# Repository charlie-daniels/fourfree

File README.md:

# fourfree - 43 key keeb

Designed because nobody sells 40-ish percent keyboards anymore.

## PCB

Created using KiCad with [marbastlib](https://github.com/ebastler/marbastlib) and a few handmade footprints.

Created Oct 2024.

## Assembly

**ProMicro goes in upsidedown on the topside!!!**
This is why the pads are on the bottom and the pin labels seem flipped from the top.

### Components 

**PCB** 

- 43x 1N4148W Diodes
- 43x Kailh Hotswap MX
- 1x Sparkfun Promicro
- 1x 2-pin Reset switch
- 1x 128x32 OLED (optional)
- 1x 2.75u PCB mount stabiliser
- 1x 2.25u PCB mount stabiliser
- 1x 2u PCB mount stabiliser

**Case**

- 14x M2 screws...?
Case still being designed but should be screw in to the pcb mounting brackets, maybe 14 was overkill...

## Firmware

This is just initial firmware made with [Keyboard Firmware Builder](https://kbfirmware.com/) by [Ruiqi Mao](https://ruiqimao.com/). The keymaps should work as expected as they are configured properly with the pinouts and key matrix.

## In Progress...

- Plate
- Case
- To see if the pcb actually works...

## Thanks

[Ben Vallack](https://www.youtube.com/channel/UC4NNPgQ9sOkBjw6GlkgCylg)'s YouTube tutorials are great.

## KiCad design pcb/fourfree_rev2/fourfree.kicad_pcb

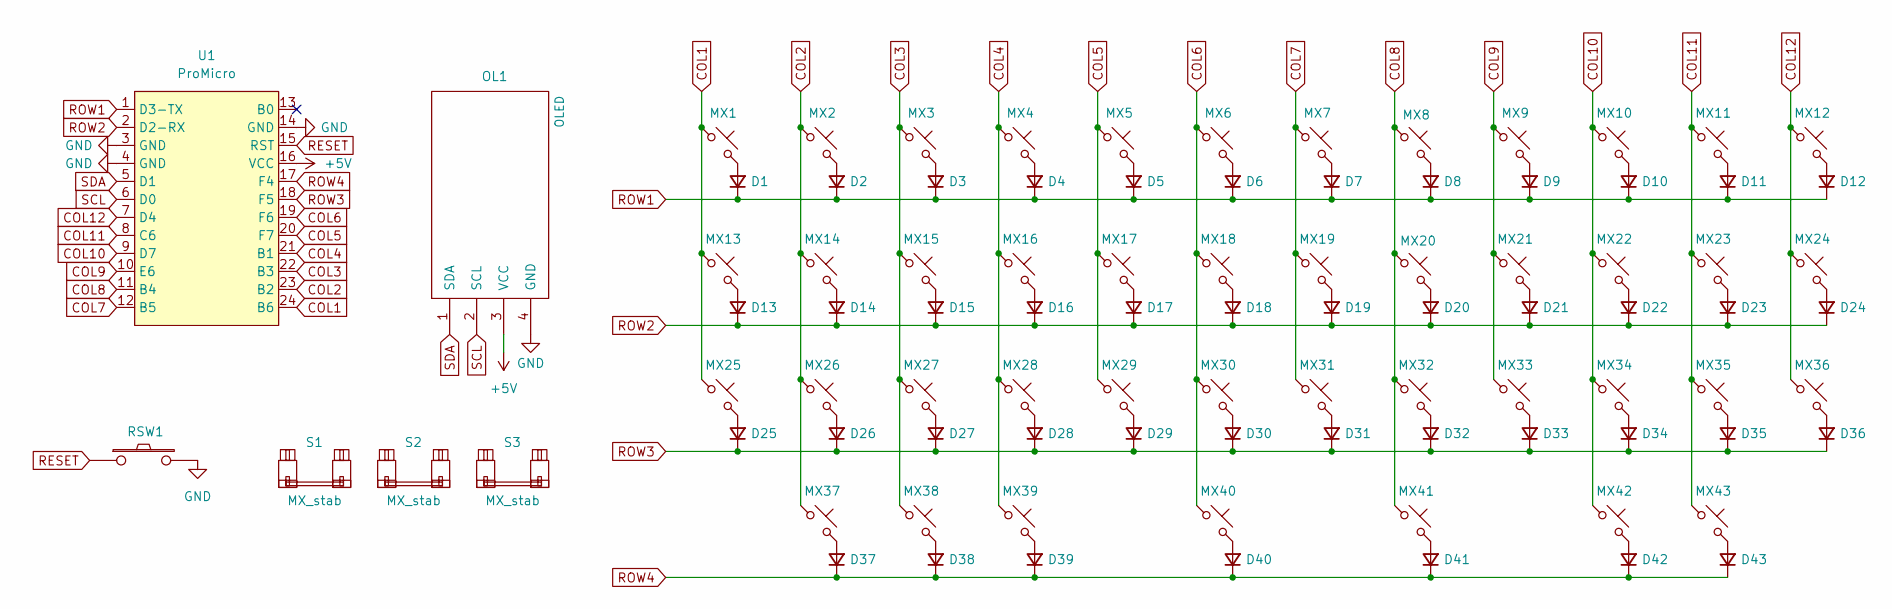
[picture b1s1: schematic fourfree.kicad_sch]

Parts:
D1, D2, D3, D4, D5, D6, D7, D8, D9, D10, D11, D12, D13, D14, D15, D16, D17, D18, D19, D20, D21, D22, D23, D24, D25, D26, D27, D28, D29, D30, D31, D32, D33, D34, D35, D36, D37, D38, D39, D40, D41, D42, D43: D_Small; D_SOD-123
MX1, MX2, MX3, MX4, MX5, MX6, MX7, MX8, MX9, MX10, MX11, MX12, MX14, MX15, MX16, MX17, MX18, MX19, MX20, MX21, MX22, MX23, MX26, MX27, MX28, MX29, MX30, MX31, MX32, MX33, MX34, MX36, MX37, MX39, MX40, MX41, MX42: MX_SW_solder; SW_MX_HS_CPG151101S11_1u
MX13, MX35, MX38, MX43: MX_SW_solder; SW_MX_HS_CPG151101S11_1.25u
MX24, MX25: MX_SW_solder; SW_MX_HS_CPG151101S11_1.75u
OL1: OLED
RSW1: SW_PUSH; ResetSW
S1: MX_stab; STAB_MX_2.75u
S2: MX_stab; STAB_MX_2u
S3: MX_stab; STAB_MX_2.25u
U1: ProMicro; ProMicro_USBup

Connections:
+5V: OL1.3 (VCC), U1.16 (VCC)
COL1: MX1.1, MX13.1, MX25.1, U1.24 (B6)
COL2: MX2.1, MX14.1, MX26.1, MX37.1, U1.23 (B2)
COL3: MX3.1, MX15.1, MX27.1, MX38.1, U1.22 (B3)
COL4: MX4.1, MX16.1, MX28.1, MX39.1, U1.21 (B1)
COL5: MX5.1, MX17.1, MX29.1, U1.20 (F7)
COL6: MX6.1, MX18.1, MX30.1, MX40.1, U1.19 (F6)
COL7: MX7.1, MX19.1, MX31.1, U1.12 (B5)
COL8: MX8.1, MX20.1, MX32.1, MX41.1, U1.11 (B4)
COL9: MX9.1, MX21.1, MX33.1, U1.10 (E6)
COL10: MX10.1, MX22.1, MX34.1, MX42.1, U1.9 (D7)
COL11: MX11.1, MX23.1, MX35.1, MX43.1, U1.8 (C6)
COL12: MX12.1, MX24.1, MX36.1, U1.7 (D4)
GND: OL1.4 (GND), RSW1.2, U1.3 (GND), U1.4 (GND), U1.14 (GND)
unnamed: D1.2 (A), MX1.2
unnamed: D2.2 (A), MX2.2
unnamed: D3.2 (A), MX3.2
unnamed: D4.2 (A), MX4.2
unnamed: D5.2 (A), MX5.2
unnamed: D6.2 (A), MX6.2
unnamed: D7.2 (A), MX7.2
unnamed: D8.2 (A), MX8.2
unnamed: D9.2 (A), MX9.2
unnamed: D10.2 (A), MX10.2
unnamed: D11.2 (A), MX11.2
unnamed: D12.2 (A), MX12.2
unnamed: D13.2 (A), MX13.2
unnamed: D14.2 (A), MX14.2
unnamed: D15.2 (A), MX15.2
unnamed: D16.2 (A), MX16.2
unnamed: D17.2 (A), MX17.2
unnamed: D18.2 (A), MX18.2
unnamed: D19.2 (A), MX19.2
unnamed: D20.2 (A), MX20.2
unnamed: D21.2 (A), MX21.2
unnamed: D22.2 (A), MX22.2
unnamed: D23.2 (A), MX23.2
unnamed: D24.2 (A), MX24.2
unnamed: D25.2 (A), MX25.2
unnamed: D26.2 (A), MX26.2
unnamed: D27.2 (A), MX27.2
unnamed: D28.2 (A), MX28.2
unnamed: D29.2 (A), MX29.2
unnamed: D30.2 (A), MX30.2
unnamed: D31.2 (A), MX31.2
unnamed: D32.2 (A), MX32.2
unnamed: D33.2 (A), MX33.2
unnamed: D34.2 (A), MX34.2
unnamed: D35.2 (A), MX35.2
unnamed: D36.2 (A), MX36.2
unnamed: D37.2 (A), MX37.2
unnamed: D38.2 (A), MX38.2
unnamed: D39.2 (A), MX39.2
unnamed: D40.2 (A), MX40.2
unnamed: D41.2 (A), MX41.2
unnamed: D42.2 (A), MX42.2
unnamed: D43.2 (A), MX43.2
RESET: RSW1.1, U1.15 (RST)
ROW1: D1.1 (K), D2.1 (K), D3.1 (K), D4.1 (K), D5.1 (K), D6.1 (K), D7.1 (K), D8.1 (K), D9.1 (K), D10.1 (K), D11.1 (K), D12.1 (K), U1.1 (D3-TX)
ROW2: D13.1 (K), D14.1 (K), D15.1 (K), D16.1 (K), D17.1 (K), D18.1 (K), D19.1 (K), D20.1 (K), D21.1 (K), D22.1 (K), D23.1 (K), D24.1 (K), U1.2 (D2-RX)
ROW3: D25.1 (K), D26.1 (K), D27.1 (K), D28.1 (K), D29.1 (K), D30.1 (K), D31.1 (K), D32.1 (K), D33.1 (K), D34.1 (K), D35.1 (K), D36.1 (K), U1.18 (F5)
ROW4: D37.1 (K), D38.1 (K), D39.1 (K), D40.1 (K), D41.1 (K), D42.1 (K), D43.1 (K), U1.17 (F4)
SCL: OL1.2 (SCL), U1.6 (D0)
SDA: OL1.1 (SDA), U1.5 (D1)

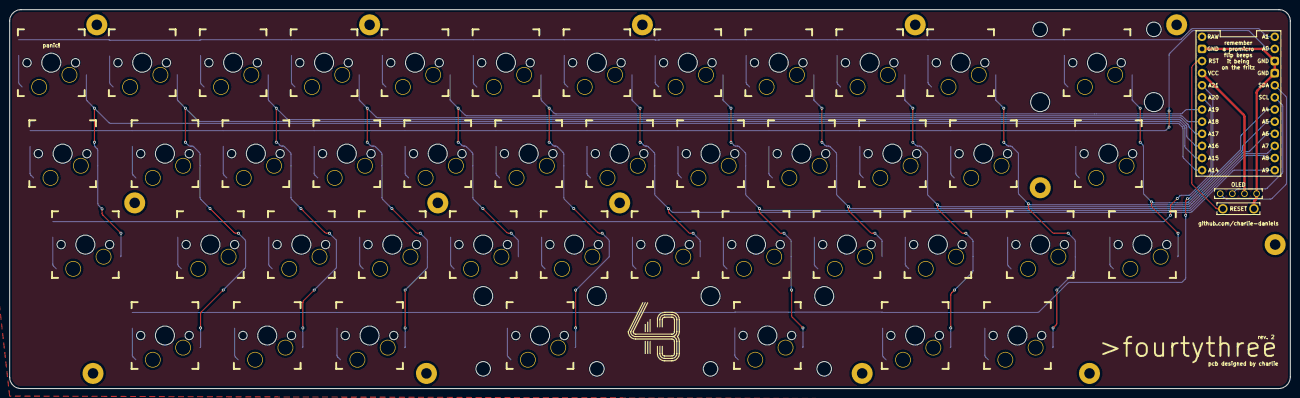
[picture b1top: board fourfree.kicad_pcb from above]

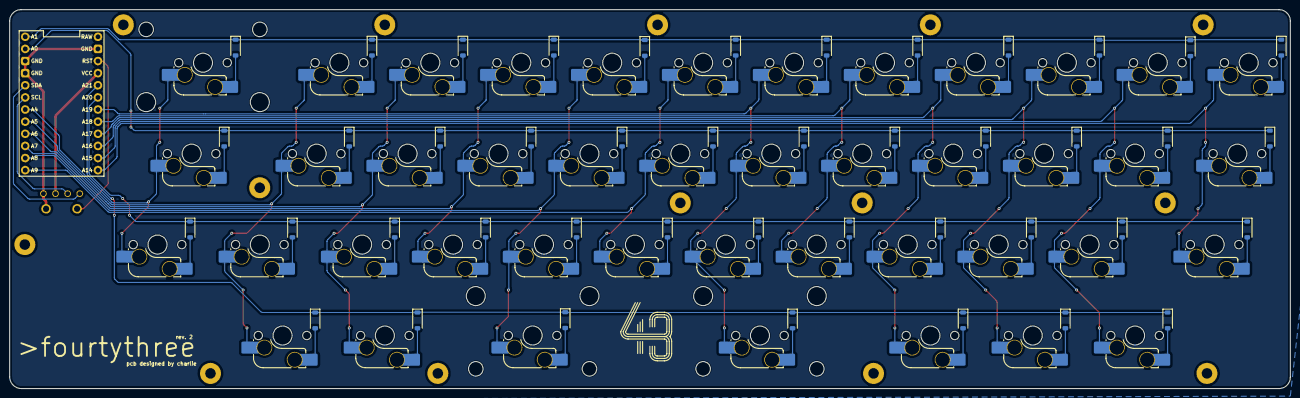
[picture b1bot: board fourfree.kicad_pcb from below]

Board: 2 copper layers, 268.3 x 79.4 mm, 92 parts (87 on the bottom side), 64 nets.

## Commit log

2024-10-28 Add pcb
2024-10-28 fix name
2024-10-28 add pcb images
2024-10-28 add readme info and layout img
2024-10-29 add initial firmware
2024-10-29 update for firmware additions
2024-10-29 fix punctuation
2024-10-29 fix titles
2024-10-30 thicken power netclass tracks
2024-10-30 add missing kicad files
2024-10-30 update gerber
